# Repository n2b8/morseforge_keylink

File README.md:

# MorseForge Keylink

**Keylink** is an open‑source hardware adapter that makes traditional Morse keys Bluetooth‑capable.

It is designed and maintained by the **MorseForge developer** as a companion device for upcoming external‑key features in the **MorseForge** app.

🌐 **MorseForge:** https://morseforge.com

---

## What is Keylink?

Keylink bridges classic Morse key hardware with modern Bluetooth‑enabled devices. It allows straight keys, paddles, and other traditional Morse inputs to transmit key events wirelessly using Bluetooth Low Energy (BLE).

Keylink is intended to:
- Enable wireless Morse key input
- Integrate directly with future MorseForge app features
- Remain compact, battery‑powered, and easy to assemble
- Be fully open source and community‑friendly

Unlike generic microcontroller dev boards, Keylink is a **purpose‑built Morse interface**.

---

## Hardware Overview — Rev B

The current hardware revision (Rev B) includes:

- **ESP32‑C3 microcontroller (Seeed XIAO form factor)**
- **3.5 mm stereo jack (SJ1‑3523N)** for Morse key input
- **Slide power switch** for battery isolation
- **JST‑PH 2.0 mm battery connector**
- LiPo battery support
- Passive input conditioning network

This revision has been fabricated via OSH Park and is undergoing validation.

---

## PCB Renders (Rev B)

### Top View

### Bottom View

> Renders generated from KiCad’s 3D viewer. These are not production photographs.

---

## Repository Structure

```
hardware/
├── keylink_revB/     # KiCad schematic + PCB layout
├── gerber/           # Manufacturing Gerbers
mobile_app/           # React Native example app
software/             # Firmware (Arduino + legacy)
```

Additional firmware and software directories will be added as development progresses.

---

## Firmware & App Integration

Keylink firmware now uses the Arduino framework and exposes the device as a BLE
HID keyboard for Vail Adapter compatibility. The sketch lives at:
`software/keylink_ble_keyboard/keylink_ble_keyboard.ino`.

Key events:
- DIT (left paddle) sends Ctrl + [
- DAH (right paddle) sends Ctrl + ]

### Flashing (Arduino)

1. Install Arduino IDE and the ESP32 board package.
2. Install the "ESP32 BLE Keyboard" library (T-vK).
3. Open `software/keylink_ble_keyboard` in Arduino IDE.
4. Select board "Seeed XIAO ESP32C3" and flash.
5. Pair the device as "Keylink" in your OS Bluetooth settings.

The prior CircuitPython UART firmware remains at `software/code.py` for
reference but is not Vail-compatible.

---

## Open Source

This project is released as open‑source hardware and software.

Licensing details will be finalized and documented explicitly, but the intent is:
- **Permissive open hardware**
- **Permissive firmware licensing**
- Community contributions welcome

---

## Disclaimer

This is experimental hardware.

No warranties are provided.  
Use at your own risk.

---

## Author

Keylink is designed and maintained by the **MorseForge developer** as part of the broader MorseForge ecosystem.

🌐 https://morseforge.com

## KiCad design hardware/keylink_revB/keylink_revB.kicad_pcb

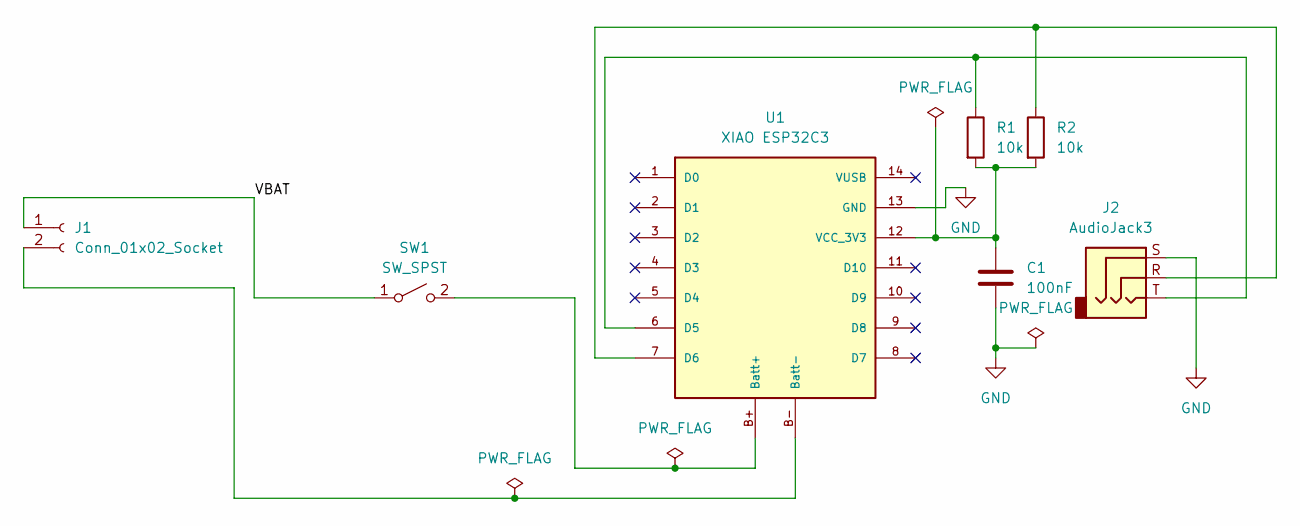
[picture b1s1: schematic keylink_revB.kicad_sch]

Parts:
C1: 100nF; C_Disc_D3.0mm_W1.6mm_P2.50mm
J1: Conn_01x02_Socket; JST_PH_S2B-PH-K_1x02_P2.00mm_Horizontal
J2: AudioJack3; Jack_3.5mm_CUI_SJ1-3523N_Horizontal
R1, R2: 10k; R_Axial_DIN0207_L6.3mm_D2.5mm_P7.62mm_Horizontal
SW1: SW_SPST; SW_Slide_SPDT_Angled_CK_OS102011MA1Q
U1: XIAO ESP32C3; xiao_esp32c3

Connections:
/VBAT: J1.1, SW1.1 (A)
GND: C1.2, J2.S, U1.13 (GND)
unnamed: J1.2, U1.B- (Batt-)
unnamed: SW1.2 (B), U1.B+ (Batt+)
unnamed: J2.T, R1.1, U1.6 (D5)
unnamed: J2.R, R2.1, U1.7 (D6)
unnamed: C1.1, R1.2, R2.2, U1.12 (VCC_3V3)

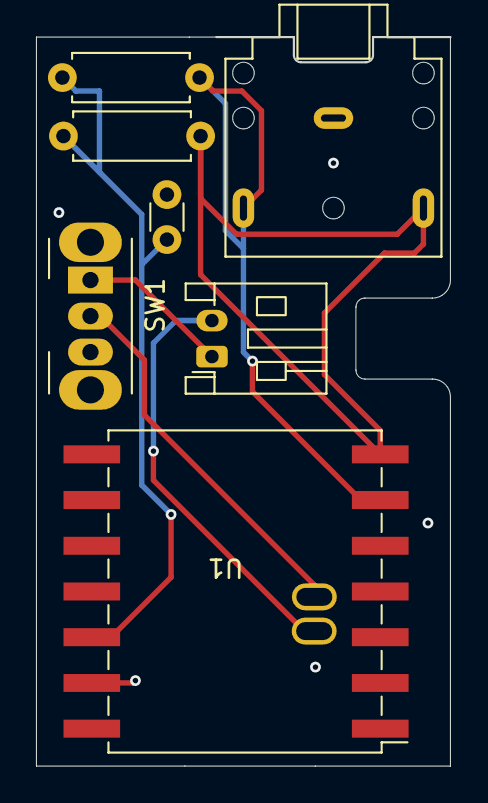
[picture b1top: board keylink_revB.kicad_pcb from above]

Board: 2 copper layers, 23.0 x 40.5 mm, 7 parts (0 on the bottom side), 7 nets.

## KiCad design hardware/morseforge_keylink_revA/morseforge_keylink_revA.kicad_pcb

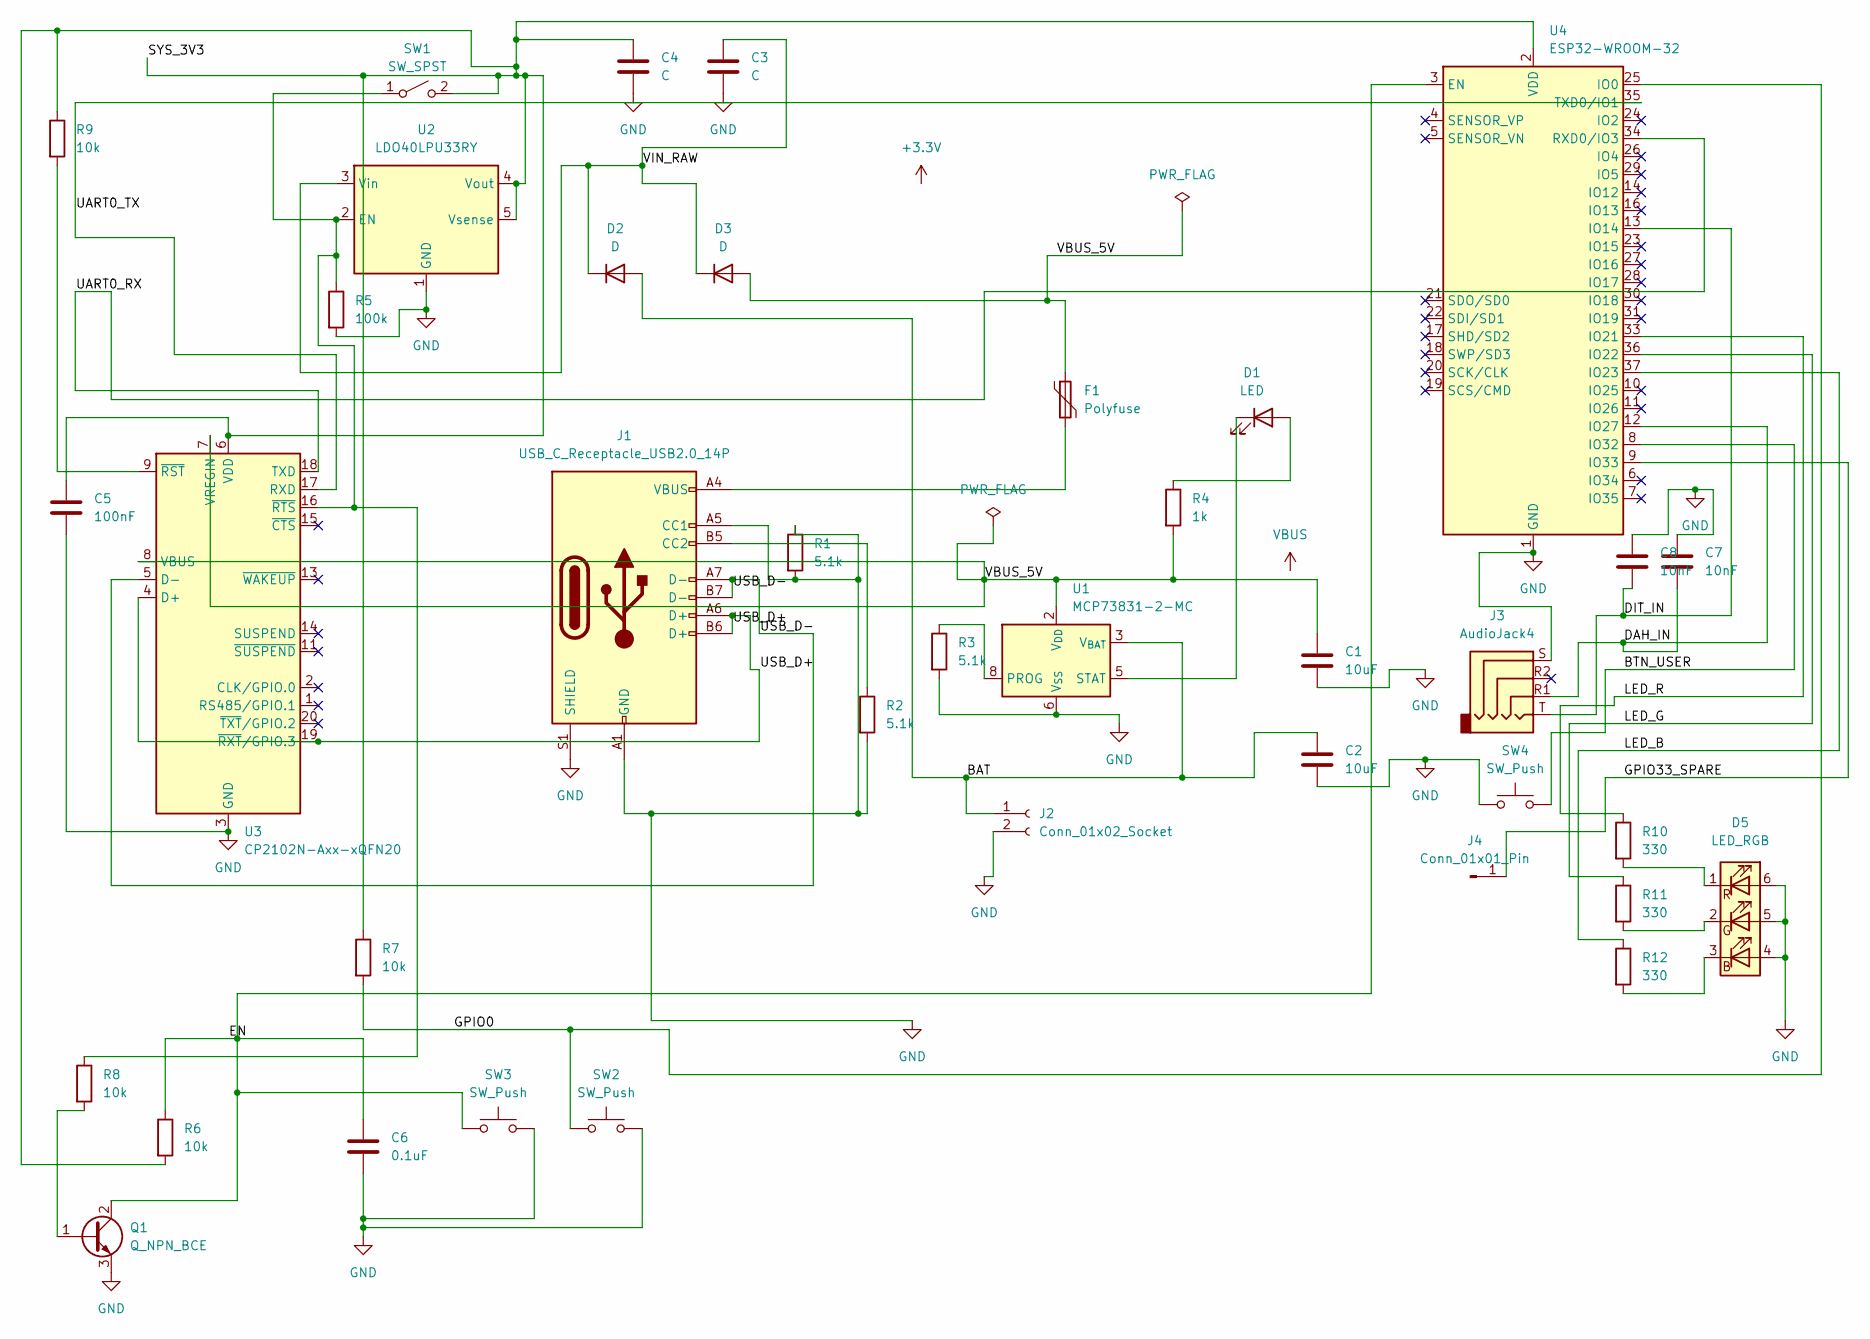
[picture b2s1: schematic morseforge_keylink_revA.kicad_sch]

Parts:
C1, C2: 10uF; C_0603_1608Metric
C3, C4: C; C_0603_1608Metric
C5: 100nF; C_0603_1608Metric
C6: 0.1uF; C_0603_1608Metric
C7, C8: 10nF; C_0603_1608Metric
D1: LED; D_SOD-123
D2, D3: D; D_SOD-123
D5: LED_RGB; LED_RGB_5050-6
F1: Polyfuse; Fuse_1206_3216Metric
J1: USB_C_Receptacle_USB2.0_14P; USB_C_Receptacle_GCT_USB4105-xx-A_16P_TopMnt_Horizontal
J2: Conn_01x02_Socket; JST_PH_S2B-PH-K_1x02_P2.00mm_Horizontal
J3: AudioJack4; Jack_3.5mm_PJ320D_Horizontal
J4: Conn_01x01_Pin; TestPoint_Pad_D1.0mm
Q1: Q_NPN_BCE; SOT-23-5_HandSoldering
R1, R2, R3: 5.1k; R_0603_1608Metric
R4: 1k; R_0603_1608Metric
R5: 100k; R_0603_1608Metric
R6, R7, R8, R9: 10k; R_0603_1608Metric
R10, R11, R12: 330; R_0603_1608Metric
SW1: SW_SPST; SW_Slide-03_Wuerth-WS-SLTV_10x2.5x6.4_P2.54mm
SW2, SW3, SW4: SW_Push; SW_SPST_TL3342
U1: MCP73831-2-MC; DFN-8-1EP_3x2mm_P0.5mm_EP1.7x1.4mm
U2: LDO40LPU33RY; DFN-6-1EP_3x3mm_P0.95mm_EP1.7x2.6mm
U3: CP2102N-Axx-xQFN20; QFN-20-1EP_3x3mm_P0.45mm_EP1.6x1.6mm
U4: ESP32-WROOM-32

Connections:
/BAT: C2.1, D2.2 (A), J2.1, U1.3 (V_{BAT}), U1.4 (V_{BAT})
/BTN_USER: SW4.2, U4.8 (IO32)
/DAH_IN: C7.2, J3.R1, U4.12 (IO27)
/DIT_IN: C8.2, J3.T, U4.13 (IO14)
/EN: C6.1, Q1.2 (C), R6.1, SW3.1, U4.3 (EN)
/GPIO0: R7.2, SW2.1, U4.25 (IO0)
/GPIO33_SPARE: J4.1, U4.9 (IO33)
/LED_B: R12.1, U4.37 (IO23)
/LED_G: R11.1, U4.36 (IO22)
/LED_R: R10.1, U4.33 (IO21)
/SYS_3V3: C4.1, C5.1, R6.2, R7.1, R9.1, SW1.2 (B), U2.4 (Vout), U2.5 (Vsense), U3.6 (VDD), U4.2 (VDD)
/UART0_RX: U3.18 (TXD), U4.34 (RXD0/IO3)
/UART0_TX: U3.17 (RXD), U4.35 (TXD0/IO1)
/USB_D+: J1.A6 (D+), J1.B6 (D+), U3.4 (D+), U3.19 (~RXT/GPIO.3)
/USB_D-: J1.A7 (D-), J1.B7 (D-), U3.5 (D-)
/VBUS_5V: C1.1, D3.2 (A), F1.1, R4.2, U1.1 (V_{DD}), U1.2 (V_{DD}), U3.7 (VREGIN), U3.8 (VBUS)
/VIN_RAW: C3.1, D2.1 (K), D3.1 (K), U2.3 (Vin)
GND: C1.2, C2.2, C3.2, C4.2, C5.2, C6.2, C7.1, C8.1, D5.4 (BA), D5.5 (GA), D5.6 (RA), J1.A1 (GND), J1.A5 (CC1), J1.A12 (GND), J1.B1 (GND), J1.B12 (GND), J1.S1 (SHIELD), J2.2, J3.S, Q1.3 (E), R1.1, R1.2, R2.2, R3.2, R5.2, SW2.2, SW3.2, SW4.1, U1.6 (V_{SS}), U2.1 (GND), U2.7 (GND), U3.3 (GND), U3.12 (GND), U3.21 (GND), U4.1 (GND), U4.15 (GND), U4.38 (GND), U4.39 (GND)
unnamed: D1.2 (A), R4.1
unnamed: D1.1 (K), U1.5 (STAT)
unnamed: D5.3 (BK), R12.2
unnamed: D5.2 (GK), R11.2
unnamed: D5.1 (RK), R10.2
unnamed: F1.2, J1.A4 (VBUS), J1.A9 (VBUS), J1.B4 (VBUS), J1.B9 (VBUS)
unnamed: J1.B5 (CC2), R2.1
unnamed: Q1.1 (B), R8.2
unnamed: R5.1, R8.1, SW1.1 (A), U2.2 (EN), U3.16 (~RTS)
unnamed: R3.1, U1.8 (PROG)
unnamed: R9.2, U3.9 (~RST)

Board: 2 copper layers, 38 parts (0 on the bottom side), 29 nets, no tracks yet.

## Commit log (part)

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2026-01-10 Prototype device software completed
2026-01-10 Starting custom pcb design
2026-01-10 PCB schematic USB-C power input block
2026-01-10 PCB BMS
2026-01-10 Fixed wire from BAT to VBAT
2026-01-10 USB-UART blocks
2026-01-10 Fix BLE scan and connection flow
2026-01-10 Adding reset and boot buttons
2026-01-10 Adding in esp32
2026-01-16 rev b board, much simpler
2026-01-16 Adding the pull up resistor footprints
2026-01-16 pcb layout completed
2026-01-16 Finalized revB.1 pcb
2026-01-16 Add .gitignore for KiCad and OS clutter
2026-01-16 Add project README for Keylink hardware
2026-01-16 Update XIAO ESP32C3 pin mapping
2026-01-21 Rewrite firmware and app for BLE keyboard input
2026-01-21 Update hardware enclosure and KiCad assets
